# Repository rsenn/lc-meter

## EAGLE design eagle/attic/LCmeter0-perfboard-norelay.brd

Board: 2 copper layers, 25 parts (0 on the bottom side), 24 nets.

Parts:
C1, C2: 1nF; C050-024X044
C3, C4: 10μF; E5-4
C5, C6: 33pF; C025-024X044
C7: 100μF; E2,5-6
C9: 100nF; C025-024X044
CLK: 1X02
IC1: PIC16F876A-X/SP; DIL28-3
JP1: 1X05
L1: 860u; 0204/5
LCD1: HD44780; MA08-1
Q1: 20MHz; HC49/S
Q2: BC548; TO92-EBC
R1, R2, R3: 100kΩ; 0204/7
R4: 47kΩ; 0204V
R5: 4.7kΩ; 0204/7
R6: 10kΩ; 0207/10
R10: 4.7kΩ; 0204V
SW1: SPST; PB-5-1
SW2: DPDT
UART: 1X03

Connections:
/LC: IC1.15, SW2.2-3
/MCLR: IC1.1, JP1.3, R10.1, SW1.4
A0: IC1.2, IC1.7, R1.2, R4.2
A1: C4.+, IC1.3, R4.1
A3: C3.+, IC1.5, R1.1, R2.2, R3.1
A4: IC1.6, R5.1
C2_CON: C2.2, Q2.C
CCAP: IC1.16, R6.1
D4: IC1.25, LCD1.5
D5: IC1.26, LCD1.6
D6: IC1.27, JP1.4, LCD1.7
D7: IC1.28, JP1.5, LCD1.8
E: IC1.24, LCD1.4
GND: C1.2, C4.-, C5.1, C6.1, C7.-, C9.2, CLK.1, IC1.8, IC1.19, JP1.1, LCD1.1, Q2.E, R2.1, SW1.2, UART.1
unnamed: CLK.2, IC1.11
unnamed: C1.1, C2.1, C3.-, L1.2, SW2.1-2
unnamed: Q2.B, R6.2
unnamed: L1.1, SW2.1-3, SW2.2-2
OSC1: C6.2, IC1.9, Q1.1
OSC2: C5.2, IC1.10, Q1.2
RS: IC1.23, LCD1.3
RX: IC1.18, UART.2
TX: IC1.17, UART.3
VCC: C7.+, C9.1, IC1.20, JP1.2, LCD1.2, R3.2, R5.2, R10.2

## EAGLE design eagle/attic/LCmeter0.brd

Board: 2 copper layers, 25 parts (0 on the bottom side), 22 nets.

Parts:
C1, C2: 1nF; C050-025X075
C3: 10μF; E2,5-6
C4: 10μF; E5-6
C5, C6: 33pF; C050-025X075
C7: 100μF; E2,5-6
C8: 10μF; E2,5-5
C9: 100nF; C025-024X044
CON1: MA07-2
D1: 1N4148; DO35-7
IC1: PIC16F876A-X/SP; DIL28-3
K2: DS2Y
L1: 100μH; 0207/10
Q1: 20MHz; HC49U70
Q2: BC548; TO92-EBC
R1, R2: 100kΩ; 0207/10
R3: 100kΩ; 0204V
R4: 47kΩ; 0207/10
R5, R10: 4.7kΩ; 0204V
R6: 0207/10
S1: TL46PO; TL4XPO
SW1: SPST; PB-5

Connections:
/LC: IC1.15, S1.6
/MCLR: IC1.1, R10.1, SW1.3
/RELAY: D1.C, K2.1, Q2.C
A0: IC1.2, IC1.7, R1.2, R4.2
A1: C4.+, IC1.3, R4.1
A3: C3.+, IC1.5, R1.1, R2.2, R3.1
A4: IC1.6, R5.1
B2: CON1.4, IC1.23
B3: CON1.6, IC1.24
B4: CON1.11, IC1.25
B5: CON1.12, IC1.26
B6: CON1.13, IC1.27
B7: CON1.14, IC1.28
unnamed: C2.2, K2.13
unnamed: C1.1, C2.1, C3.-, L1.2, S1.1
unnamed: Q2.B, R6.2
unnamed: L1.1, S1.3, S1.4
OSC1: C6.2, IC1.9, Q1.1
OSC2: C5.2, IC1.10, Q1.2
RC5: IC1.16, R6.1
VDD: C7.+, C8.+, C9.1, IC1.20, R3.2, R5.2, R10.2
VSS: C1.2, C4.-, C5.1, C6.1, C7.-, C8.-, C9.2, CON1.1, CON1.5, D1.A, IC1.8, IC1.19, K2.9, K2.16, Q2.E, R2.1, SW1.1

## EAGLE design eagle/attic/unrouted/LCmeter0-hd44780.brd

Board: 2 copper layers, 26 parts (0 on the bottom side), 24 nets.

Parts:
C1: 1nF; C050-025X075
C2: 10uF; E5-4
C3: 10uF; E5-5
C4: C025-024X044
C5: E2,5-6E
C6, C7: 22pF; C050-024X044
CCAL: 1nF; C050-025X075
D1: 1N4148; DO35-7
ICSP: FE05-1
J1: 22-27-2021-02; 6410-02
K1: DS2Y
L2: 100uH; 0204/7
LCD: FE08
Q1: HC49/S
R1, R2: 100k; 0204V
R3: 100k; 0204/7
R4: 47k; 0204V
R5: 4.7k; 0204/5
R11: 4.7k; 0204V
R12: 4.7k; 0207/10
S1: 9450-2
T1: TO92-CBE
U$2: PB-5-2; PB-5-1
U$3: PIC16F876A-X/SP-COMP-B; DIL28-3

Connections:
+5V: C4.1, C5.+, D1.C, ICSP.2, K1.1, LCD.2, R1.2, R5.2, R11.2, U$3.20
GND: C1.2, C3.-, C4.2, C5.-, C6.2, C7.2, ICSP.1, K1.4, R2.1, T1.E, U$2.2, U$3.8, U$3.19
L/C: S1.4, U$3.15
MCLR: ICSP.3, R11.1, U$2.4, U$3.1
unnamed: LCD.3, U$3.23
unnamed: LCD.4, U$3.24
unnamed: LCD.5, U$3.25
unnamed: LCD.6, U$3.26
unnamed: J1.1, S1.2
unnamed: R5.1, U$3.6
unnamed: J1.2, S1.5
unnamed: C7.1, Q1.2, U$3.10
unnamed: C6.1, Q1.1, U$3.9
unnamed: R3.1, R4.2, U$3.2, U$3.7
unnamed: R12.2, T1.B
unnamed: D1.A, K1.16, T1.C
unnamed: CCAL.2, K1.8
unnamed: C1.1, C2.+, CCAL.1, L2.2, S1.3
unnamed: L2.1, S1.1, S1.6
PGC: ICSP.4, LCD.7, U$3.27
PGD: ICSP.5, LCD.8, U$3.28
RA1: C3.+, R4.1, U$3.3
RA3: C2.-, R1.1, R2.2, R3.2, U$3.5
RELAY: R12.1, U$3.16

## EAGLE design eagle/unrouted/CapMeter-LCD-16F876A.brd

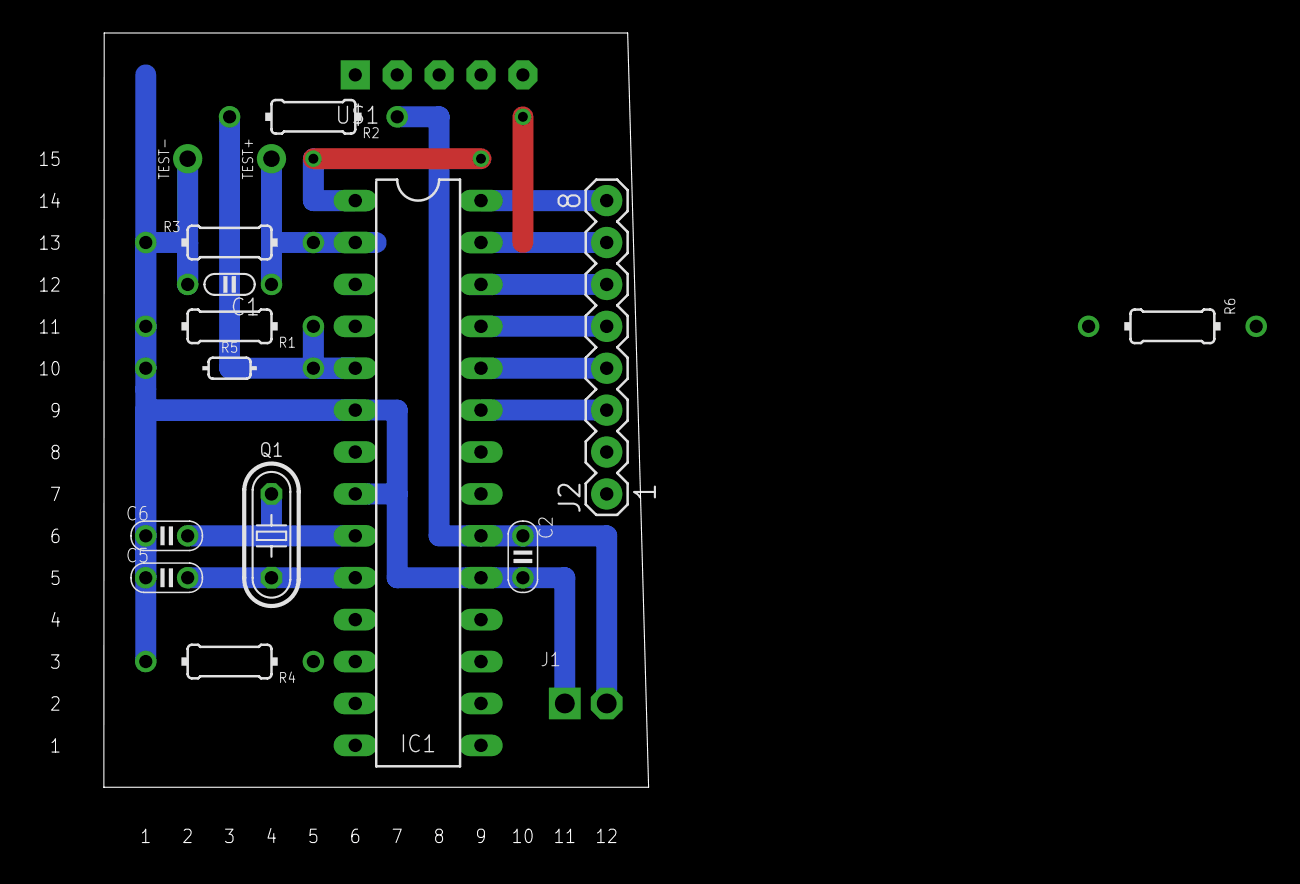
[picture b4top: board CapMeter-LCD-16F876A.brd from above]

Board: 2 copper layers, 33.0 x 45.7 mm, 17 parts (0 on the bottom side), 15 nets.

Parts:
C1: 270pF; C050-020X036
C2: 100nF; C025-020X036
C5, C6: 33pF; C025-020X036
IC1: PIC16F876A-X/SP-COMPDIL28-3/V; DIL28-3/V
J1: CONN-2P2P/H; CONN-2P
J2: LCD-8PIN; 1X8
Q1: 20MHz; HC49
R1, R2, R4: 1.5k; 0204/10
R3: 10k; 0204/10
R5: 1.5k; 0202/10
R6: 10k; 0204/10-V
TEST+: SPAD
TEST-: SPAD
U$1: PIC-ICSPICSP; PIC-ICSP

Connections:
D4: IC1.25, J2.5
D5: IC1.26, J2.6
D6: IC1.27, J2.7, U$1.4
D7: IC1.28, J2.8, U$1.5
E: IC1.24, J2.4
GND: C1.2, C2.2, C5.1, C6.1, IC1.8, IC1.19, J1.1, R1.2, TEST-.1, U$1.1
unnamed: IC1.2, R3.2, TEST+.1
unnamed: IC1.6, R3.1, R4.2, R5.1
unnamed: IC1.5, R1.1, R2.2, R5.2
unnamed: IC1.1, R6.2, U$1.3
OSC1: C6.2, IC1.9, Q1.2
OSC2: C5.2, IC1.10, Q1.1
RC1: IC1.12, R4.1
RS: IC1.23, J2.3
VCC: C2.1, IC1.20, J1.2, R2.1, R6.1, U$1.2
